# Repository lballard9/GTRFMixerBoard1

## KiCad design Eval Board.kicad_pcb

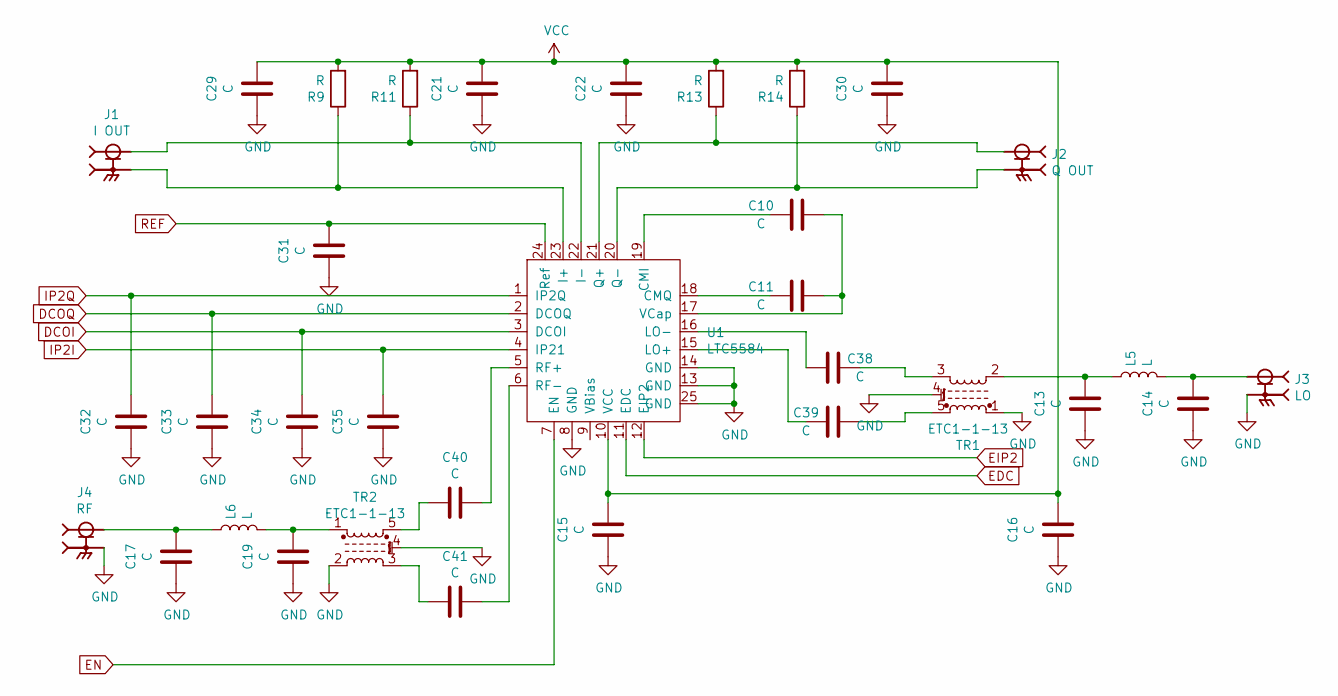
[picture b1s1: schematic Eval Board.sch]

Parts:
C10, C11, C13, C14, C15, C16, C17, C19, C21, C22, C29, C30, C31, C32, C33, C34, C35, C38, C39, C40, C41: C; C_0603_1608Metric
J1: I OUT; SAMTEC_SMA-J-P-H-ST-EM1; PARTREV G
J2: Q OUT; SAMTEC_SMA-J-P-H-ST-EM1; PARTREV G
J3: LO; SAMTEC_SMA-J-P-H-ST-EM1; PARTREV G
J4: RF; SAMTEC_SMA-J-P-H-ST-EM1; PARTREV G
L5, L6: L; L_0603_1608Metric
R9, R11, R13, R14: R; R_0603_1608Metric
TR1, TR2: ETC1-1-13; Transformer_MACOM_SM-22
U1: LTC5584; VQFN-24-1EP_4x4mm_P0.5mm_EP2.45x2.45mm

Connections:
DCOI: C34.1, U1.3 (DCOI)
DCOQ: C33.1, U1.2 (DCOQ)
EDC: U1.11 (EDC)
EIP2: U1.12 (EIP2)
EN: U1.7 (EN)
GND: C13.2, C14.2, C15.2, C16.2, C17.2, C19.2, C21.2, C22.2, C29.2, C30.2, C31.2, C32.2, C33.2, C34.2, C35.2, J3.2_1, J3.2_2, J3.3_1, J3.3_2, J4.2_1, J4.2_2, J4.3_1, J4.3_2, TR1.1, TR1.4 (MP), TR2.2, TR2.4 (MP), U1.8 (GND), U1.13 (GND), U1.14 (GND), U1.25 (GND)
IP2I: C35.1, U1.4 (IP21)
IP2Q: C32.1, U1.1 (IP2Q)
unnamed: C10.1, C11.1, U1.17 (VCap)
unnamed: C10.2, U1.19 (CMI)
unnamed: C11.2, U1.18 (CMQ)
unnamed: C13.1, L5.1, TR1.2
unnamed: C14.1, J3.1, L5.2
unnamed: C17.1, J4.1, L6.1
unnamed: C19.1, L6.2, TR2.1
unnamed: C38.1, TR1.3
unnamed: C38.2, U1.16 (LO-)
unnamed: C39.1, TR1.5
unnamed: C39.2, U1.15 (LO+)
unnamed: C40.1, U1.5 (RF+)
unnamed: C40.2, TR2.5
unnamed: C41.1, U1.6 (RF-)
unnamed: C41.2, TR2.3
unnamed: J1.1, R11.1, U1.22 (I-)
unnamed: J1.2_1, J1.2_2, J1.3_1, J1.3_2, R9.1, U1.23 (I+)
unnamed: J2.1, R13.1, U1.21 (Q+)
unnamed: J2.2_1, J2.2_2, J2.3_1, J2.3_2, R14.1, U1.20 (Q-)
REF: C31.1, U1.24 (Ref)
VCC: C15.1, C16.1, C21.1, C22.1, C29.1, C30.1, R9.2, R11.2, R13.2, R14.2, U1.10 (VCC)

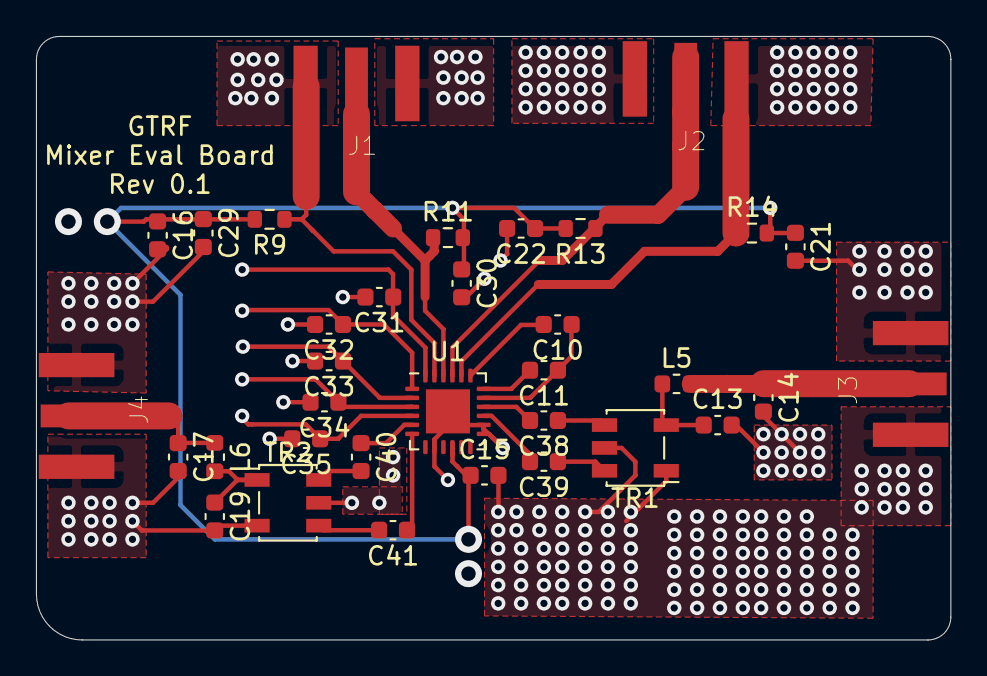
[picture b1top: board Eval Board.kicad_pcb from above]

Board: 2 copper layers, 50.8 x 33.5 mm, 34 parts (0 on the bottom side), 26 nets.

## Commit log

2021-01-23 first add
2021-01-24 Rev 0.1
